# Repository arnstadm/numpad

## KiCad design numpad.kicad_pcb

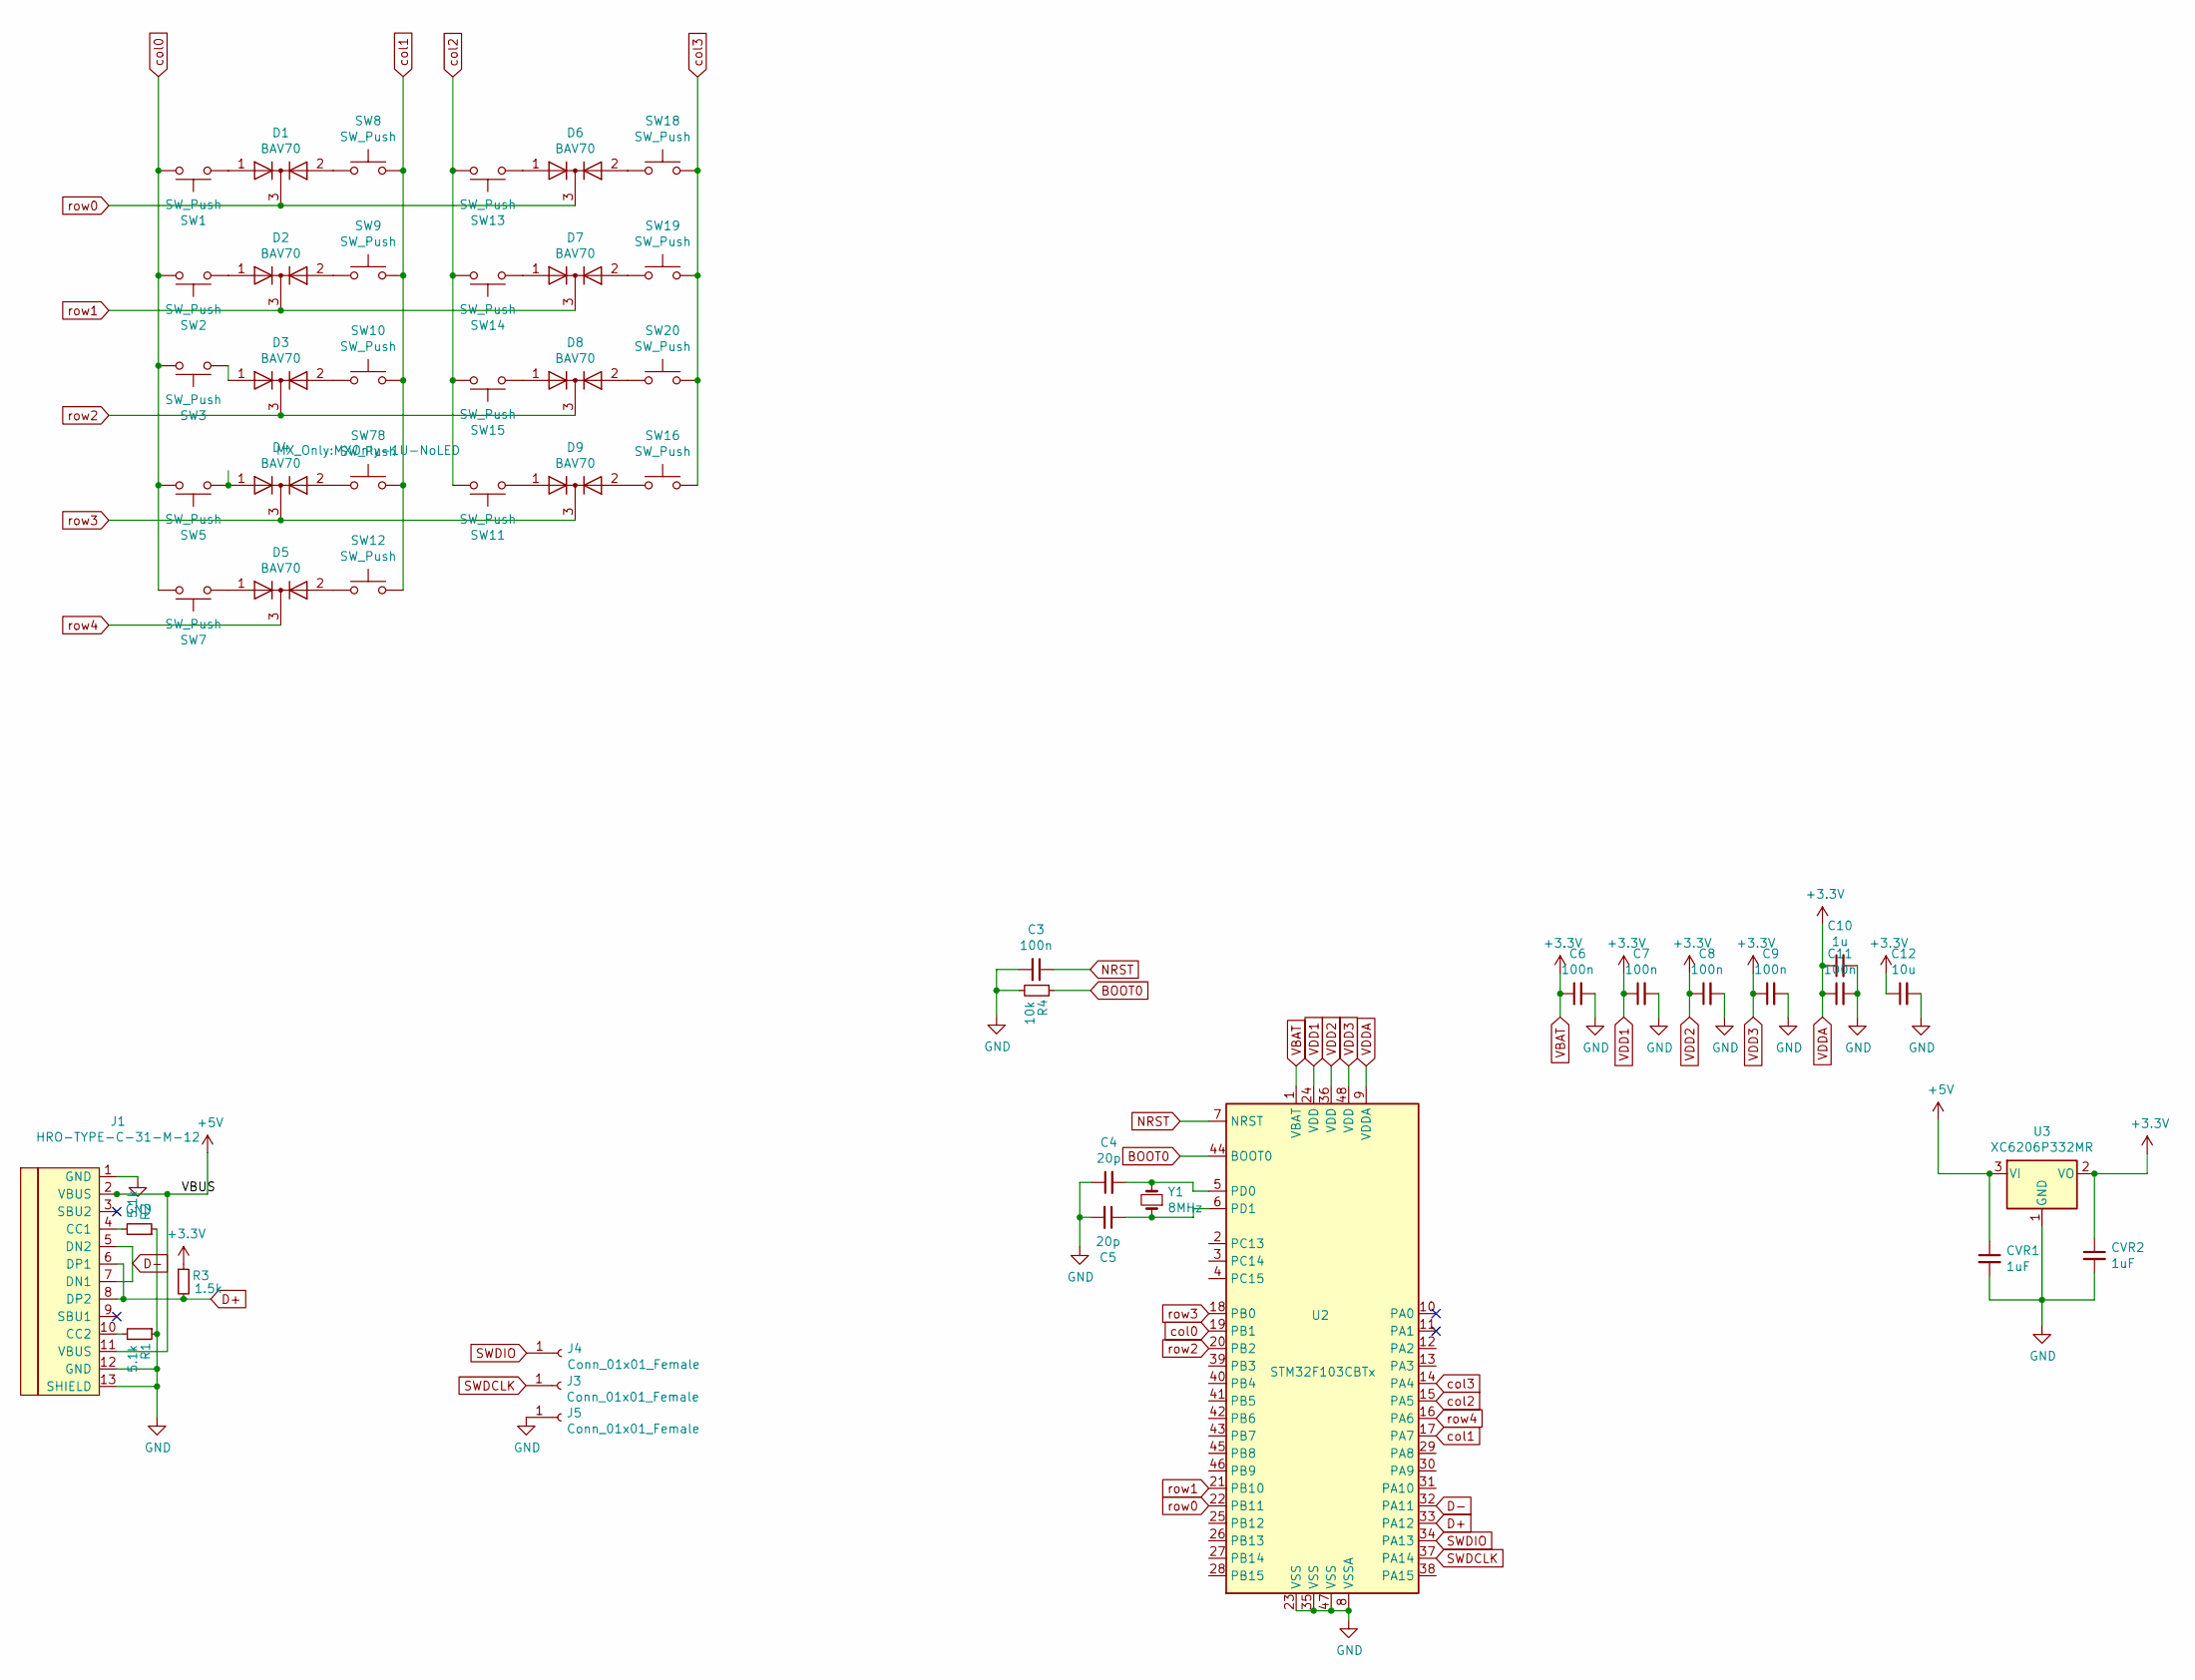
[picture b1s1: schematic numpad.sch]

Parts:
C3, C6, C7, C8, C9, C11: 100n; C_0402_1005Metric
C4, C5: 20p; C_0402_1005Metric
C10: 1u; C_0402_1005Metric
C12: 10u; C_0402_1005Metric
CVR1, CVR2: 1uF; C_0402_1005Metric
D1, D2, D3, D4, D5, D6, D7, D8, D9: BAV70; SOT-23
J1: HRO-TYPE-C-31-M-12; HRO-TYPE-C-31-M-12-HandSoldering
J3, J4, J5: Conn_01x01_Female; TestPoint_Pad_D1.5mm
R1, R2: 5.1k; R_0402_1005Metric
R3: 1.5k; R_0402_1005Metric
R4: 10k; R_0402_1005Metric
SW1, SW2, SW3, SW5, SW8, SW9, SW10, SW11, SW12, SW13, SW14, SW15, SW18, SW19, SW20, SW78: SW_Push; MXOnly-1U-NoLED
SW7, SW16: SW_Push; MXOnly-2U-ReversedStabilizers-NoLED
U2: STM32F103CBTx; LQFP-48_7x7mm_P0.5mm
U3: XC6206P332MR; SOT-23
Y1: 8MHz; Crystal_SMD_5032-2Pin_5.0x3.2mm

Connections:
+5V: CVR1.1, J1.2 (VBUS), J1.11 (VBUS), U3.3 (VI)
BOOT0: R4.1, U2.44 (BOOT0)
D+: J1.6 (DP1), J1.8 (DP2), R3.2, U2.33 (PA12)
D-: J1.5 (DN2), J1.7 (DN1), U2.32 (PA11)
GND: C3.2, C4.1, C5.2, C6.2, C7.2, C8.2, C9.2, C10.2, C11.2, C12.2, CVR1.2, CVR2.2, J1.1 (GND), J1.12 (GND), J1.13 (SHIELD), J5.1, R1.1, R2.1, R4.2, U2.8 (VSSA), U2.23 (VSS), U2.35 (VSS), U2.47 (VSS), U3.1 (GND); also elsewhere on the board
NRST: C3.1, U2.7 (NRST)
unnamed: C4.2, U2.5 (PD0), Y1.2
unnamed: C5.1, U2.6 (PD1), Y1.1
unnamed: D1.1 (A), SW1.1
unnamed: D1.2 (A), SW8.1
unnamed: D2.1 (A), SW2.1
unnamed: D2.2 (A), SW9.1
unnamed: D3.1 (A), SW3.1
unnamed: D3.2 (A), SW10.1
unnamed: D4.1 (A), SW5.1
unnamed: D4.2 (A), SW78.1
unnamed: D5.1 (A), SW7.1
unnamed: D5.2 (A), SW12.1
unnamed: D6.1 (A), SW13.1
unnamed: D6.2 (A), SW18.1
unnamed: D7.1 (A), SW14.1
unnamed: D7.2 (A), SW19.1
unnamed: D8.1 (A), SW15.1
unnamed: D8.2 (A), SW20.1
unnamed: D9.1 (A), SW11.1
unnamed: D9.2 (A), SW16.1
unnamed: J1.4 (CC1), R2.2
unnamed: J1.10 (CC2), R1.2
SWDCLK: J3.1, U2.37 (PA14); also elsewhere on the board
SWDIO: J4.1, U2.34 (PA13); also elsewhere on the board
VBAT: C6.1, C7.1, C8.1, C9.1, C10.1, C11.1, C12.1, CVR2.1, R3.1, U2.1 (VBAT), U2.9 (VDDA), U2.24 (VDD), U2.36 (VDD), U2.48 (VDD), U3.2 (VO)
col0: SW1.2, SW2.2, SW3.2, SW5.2, SW7.2, U2.19 (PB1)
col1: SW8.2, SW9.2, SW10.2, SW12.2, SW78.2, U2.17 (PA7)
col2: SW11.2, SW13.2, SW14.2, SW15.2, U2.15 (PA5)
col3: SW16.2, SW18.2, SW19.2, SW20.2, U2.14 (PA4)
row0: D1.3 (K), D6.3 (K), U2.22 (PB11)
row1: D2.3 (K), D7.3 (K), U2.21 (PB10)
row2: D3.3 (K), D8.3 (K), U2.20 (PB2)
row3: D4.3 (K), D9.3 (K), U2.18 (PB0)
row4: D5.3 (K), U2.16 (PA6)

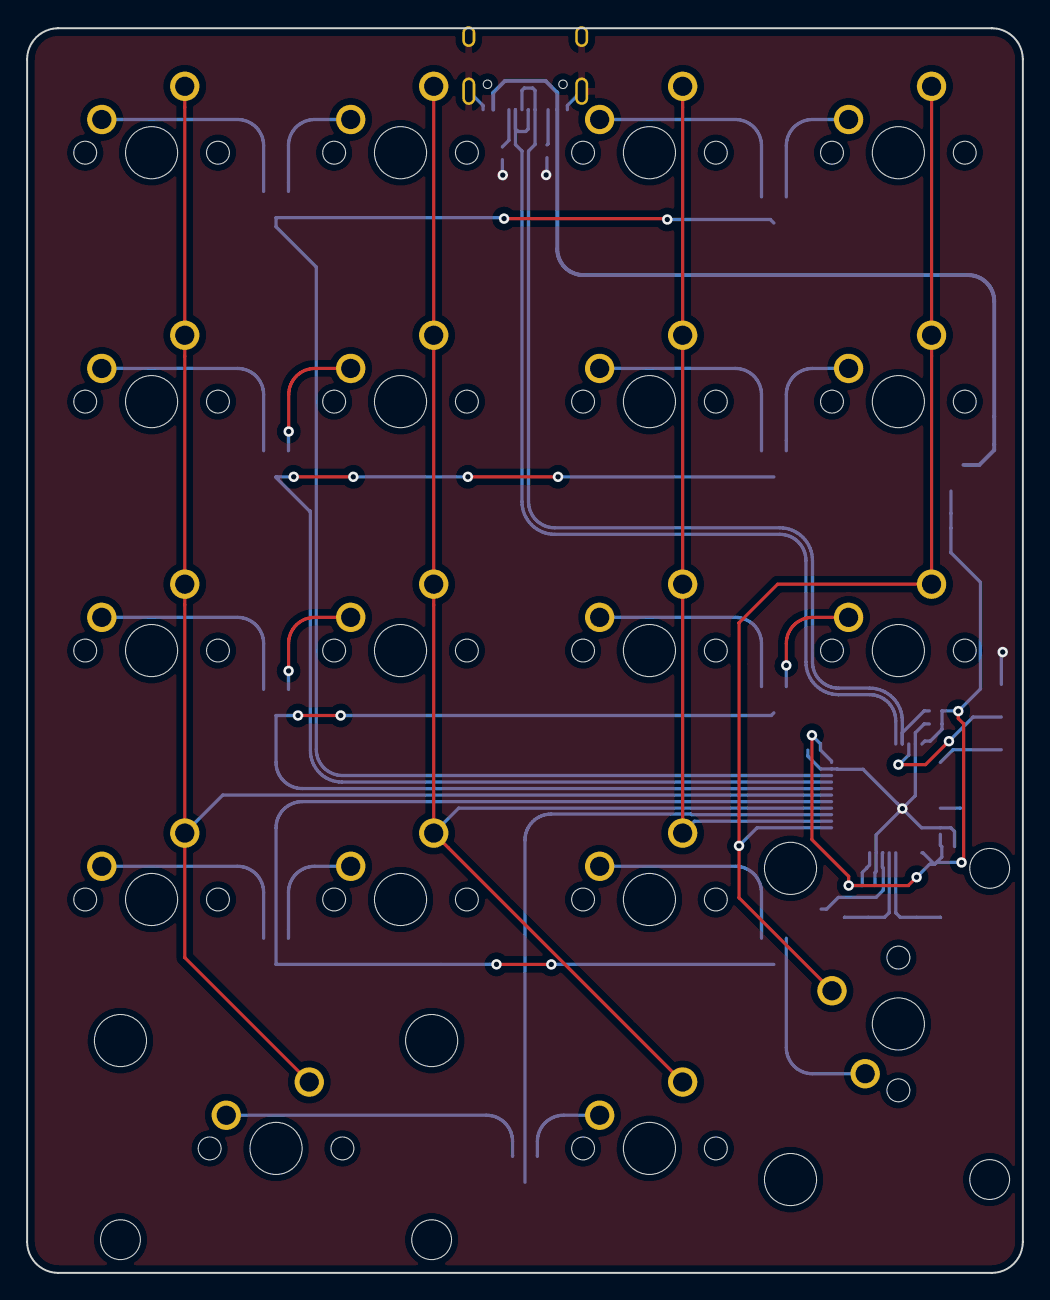
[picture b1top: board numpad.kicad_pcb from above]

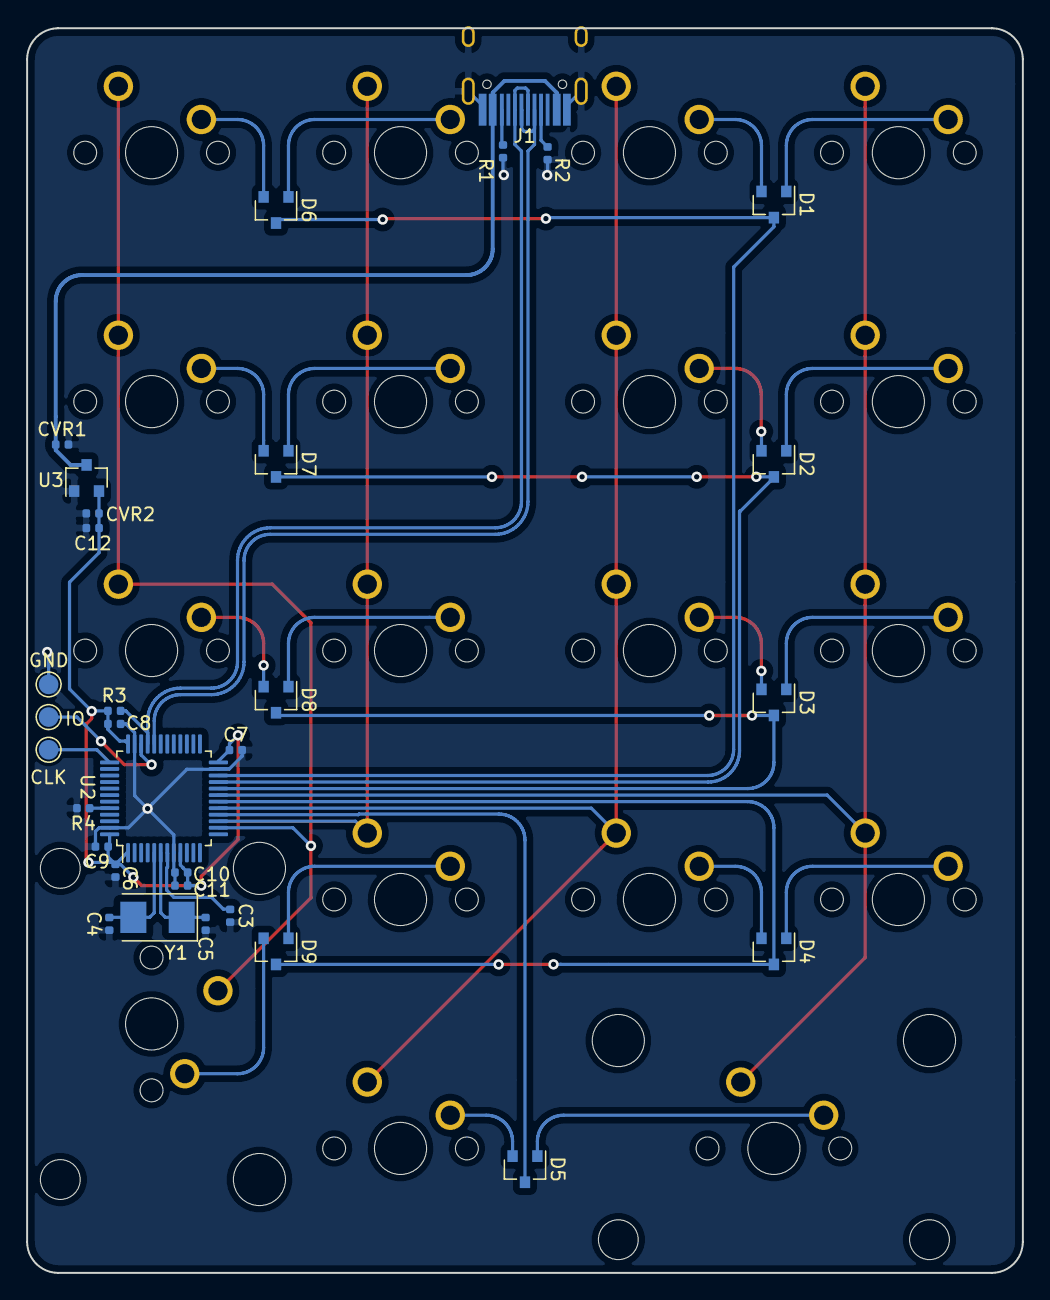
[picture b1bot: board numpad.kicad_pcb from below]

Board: 2 copper layers, 76.2 x 95.2 mm, 50 parts (32 on the bottom side), 40 nets.

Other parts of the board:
CLK: Conn_01x01_Female; TestPoint_Pad_D1.5mm
GND: Conn_01x01_Female; TestPoint_Pad_D1.5mm
IO: Conn_01x01_Female; TestPoint_Pad_D1.5mm

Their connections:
GND: GND.1; also elsewhere on the board
SWDCLK: CLK.1; also elsewhere on the board
SWDIO: IO.1; also elsewhere on the board

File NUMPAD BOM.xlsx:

Comment | Designator | Footprint | LCSC Part #
1u | C10, CVR1,CVR2 | Capacitor_SMD:C_0402_1005Metric | C52923
10u | C12 | Capacitor_SMD:C_0402_1005Metric | C15525
100n | C3,C6,C7,C8,C9,C11 | Capacitor_SMD:C_0402_1005Metric | C1525
20p | C4,C5 | Capacitor_SMD:C_0402_1005Metric | C1554
BAV70 | D1,D2,D3,D4,D5,D6,D7,D8,D9 | Package_TO_SOT_SMD:SOT-23 | C68978
5.1k | R1,R2 | Resistor_SMD:R_0402_1005Metric | C25905
1.5k | R3 | Resistor_SMD:R_0402_1005Metric | C25867
10k | R4 | Resistor_SMD:R_0402_1005Metric | C25744
STM32F103CBTx | U2 | Package_QFP:LQFP-48_7x7mm_P0.5mm | C8304
XC6206P322MR | U3 | Package_TO_SOT_SMD:SOT-23 | C5446
8MHz | Y1 | Crystal:Crystal_SMD_5032-2Pin_5.0x3.2mm | C115962

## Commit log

2021-01-09 numpad
2021-01-09 Create LICENSE
2021-01-09 added pictures
2021-01-10 silkscreen location
